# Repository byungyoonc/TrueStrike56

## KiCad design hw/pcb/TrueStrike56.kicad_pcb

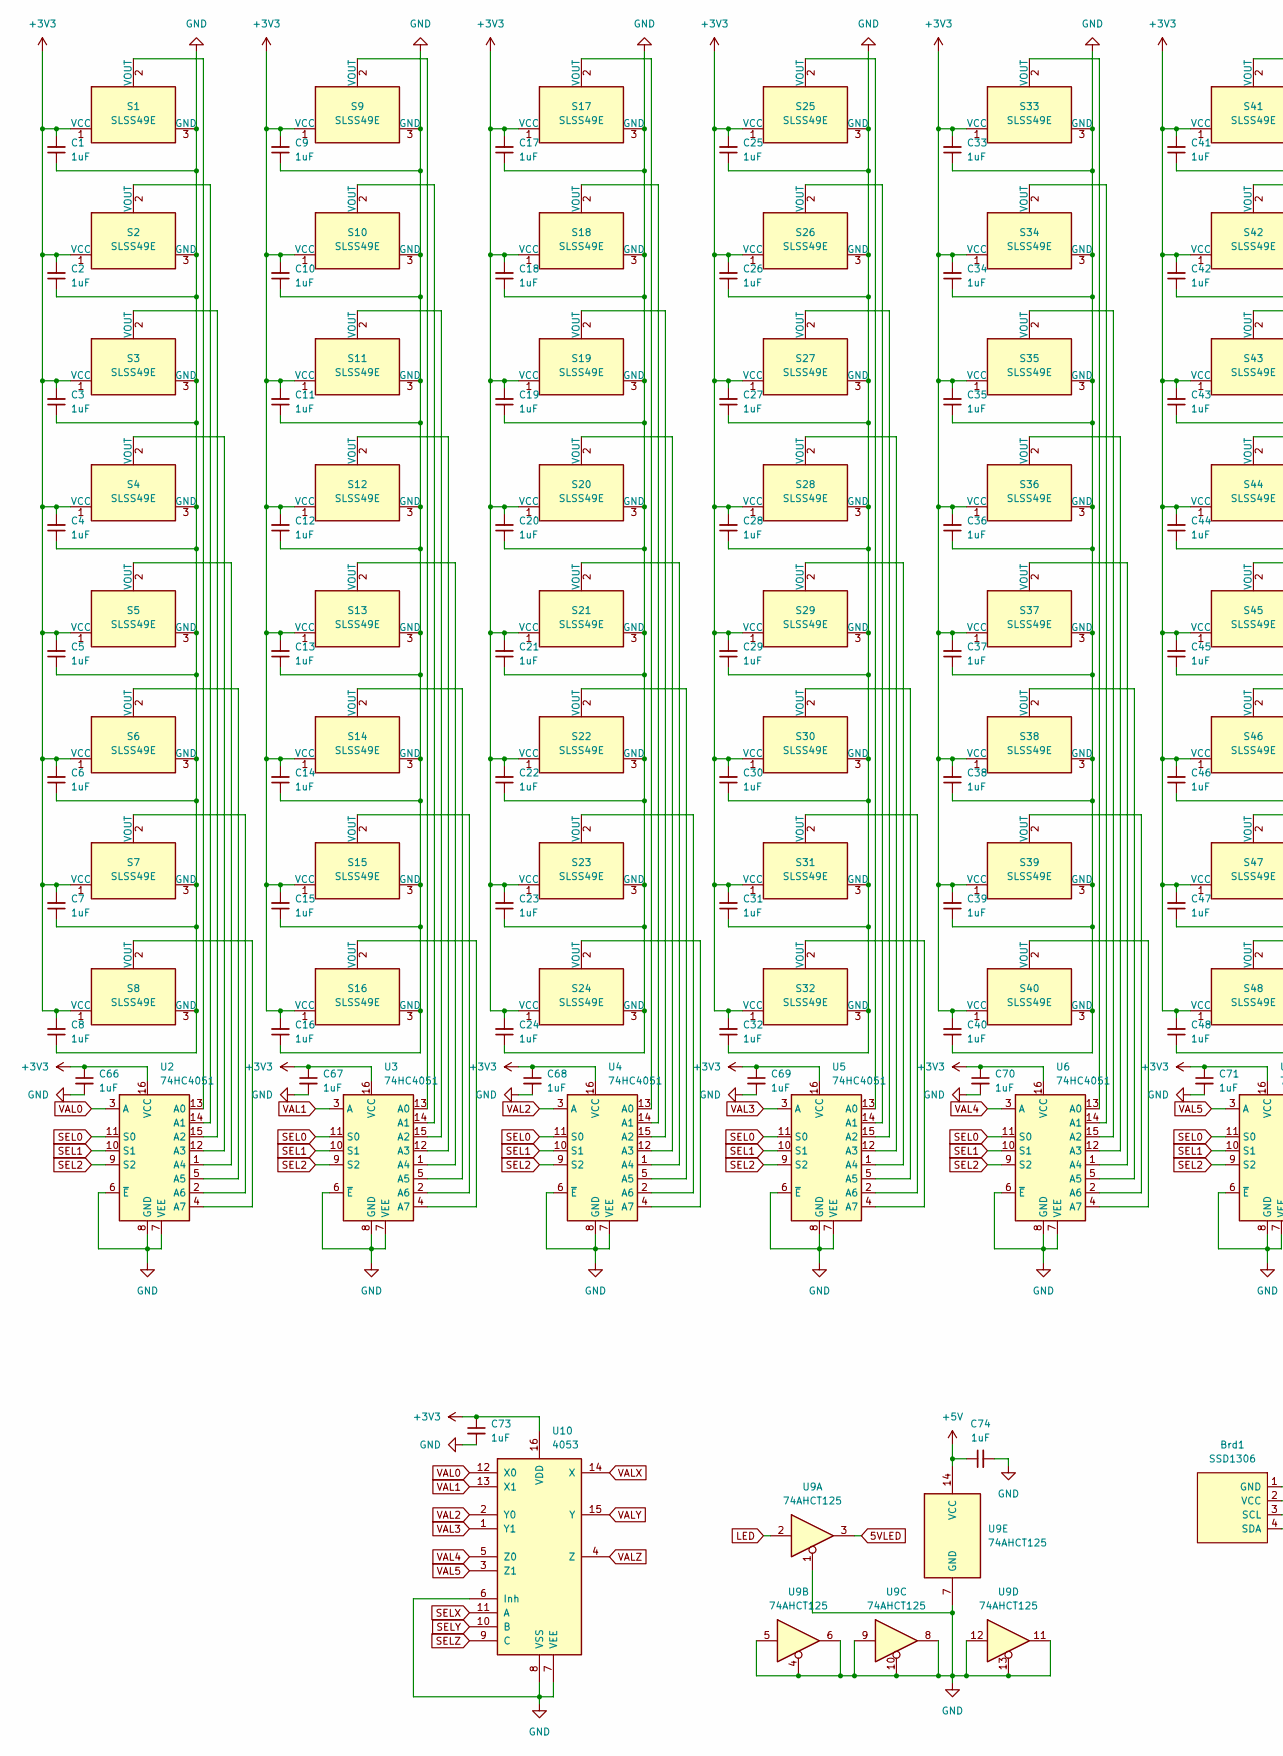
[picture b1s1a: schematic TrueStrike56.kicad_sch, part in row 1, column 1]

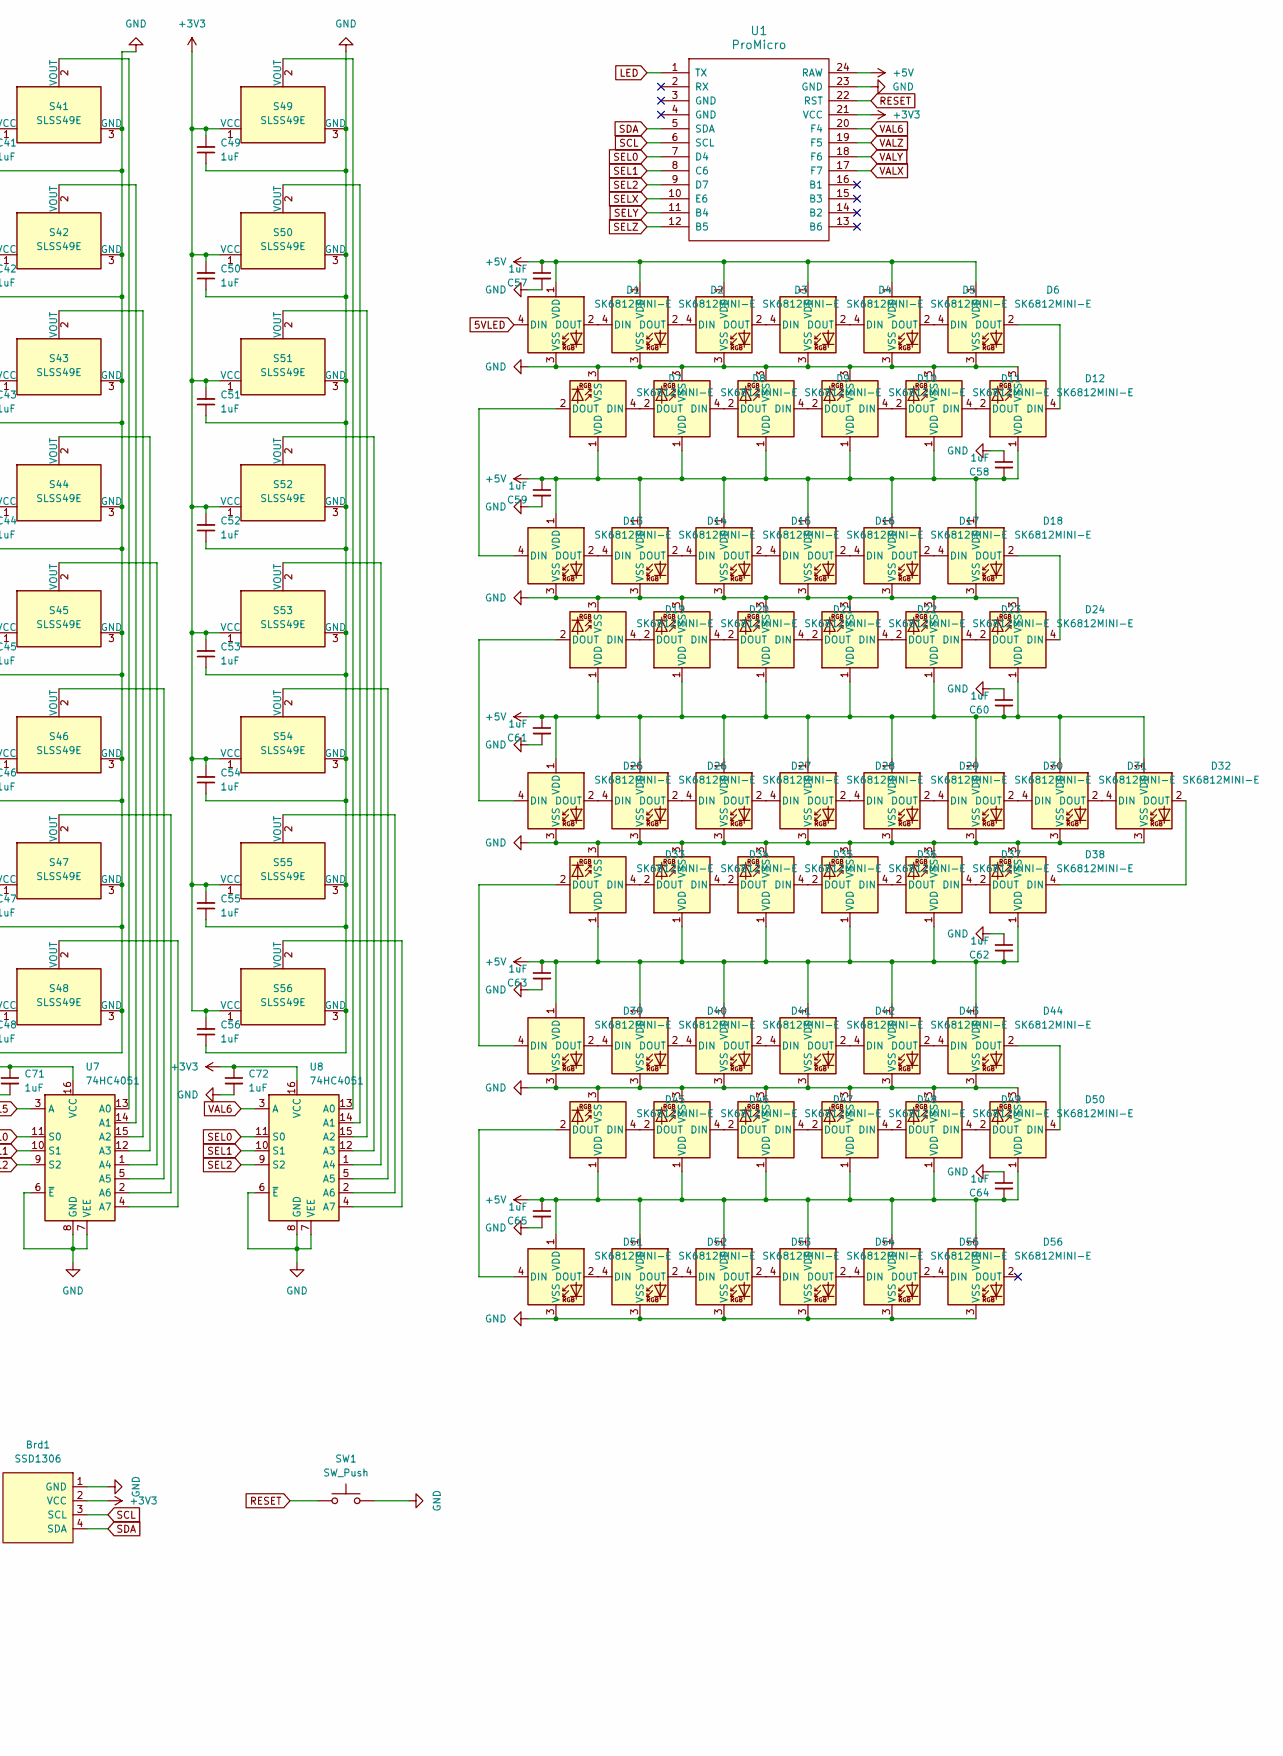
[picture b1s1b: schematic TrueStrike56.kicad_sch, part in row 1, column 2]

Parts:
Brd1: SSD1306; 128x64OLED
C1, C2, C3, C4, C5, C6, C7, C8, C9, C10, C11, C12, C13, C14, C15, C16, C17, C18, C19, C20, C21, C22, C23, C24, C25, C26, C27, C28, C29, C30, C31, C32, C33, C34, C35, C36, C37, C38, C39, C40, C41, C42, C43, C44, C45, C46, C47, C48, C49, C50, C51, C52, C53, C54, C55, C56, C57, C58, C59, C60, C61, C62, C63, C64, C65, C66, C67, C68, C69, C70, C71, C72, C73, C74: 1uF; C_0805_2012Metric_Pad1.18x1.45mm_HandSolder; LCSC Part # C28233
D1, D2, D3, D4, D5, D6, D13, D14, D15, D16, D17, D18, D33, D34, D35, D36, D37, D38, D45, D46, D47, D48, D49, D50: SK6812MINI-E; SK6812MINI-E_nusumi; LCSC Part # C5149201
D7, D8, D9, D10, D11, D12, D19, D20, D21, D22, D23, D24, D25, D26, D27, D28, D29, D30, D31, D32, D39, D40, D41, D42, D43, D44, D51, D52, D53, D54, D55, D56: SK6812MINI-E; SK6812MINI-E_nusumi_Rotated; LCSC Part # C5149201
S1, S2, S3, S4, S5, S6, S7, S8, S9, S10, S11, S12, S13, S14, S15, S16, S17, S18, S19, S20, S21, S22, S23, S24, S25, S26, S27, S28, S29, S30, S31, S32, S33, S34, S35, S36, S37, S38, S39, S40, S41, S42, S43, S44, S45, S46, S47, S48, S49, S50, S51, S54, S55, S56: SLSS49E; HE-Switch-1U; LCSC Part # C126669
S52, S53: SLSS49E; HE-Switch-1.5U; LCSC Part # C126669
SW1: SW_Push; SW_Push_1P1T_XKB_TS-1187A; LCSC Part # C318884
U1: ProMicro
U2, U3, U4, U5, U6, U7, U8: 74HC4051; SOIC-16_3.9x9.9mm_P1.27mm; LCSC Part # C85220
U9: 74AHCT125; SOIC-14_3.9x8.7mm_P1.27mm; LCSC Part # C155176
U10: 4053; SOIC-16_3.9x9.9mm_P1.27mm; LCSC Part # C5647

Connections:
5VLED: D1.4 (DIN), U9.3
+3V3: Brd1.2 (VCC), C1.2, C2.2, C3.2, C4.2, C5.2, C6.2, C7.2, C8.2, C9.2, C10.2, C11.2, C12.2, C13.2, C14.2, C15.2, C16.2, C17.2, C18.2, C19.2, C20.2, C21.2, C22.2, C23.2, C24.2, C25.2, C26.2, C27.2, C28.2, C29.2, C30.2, C31.2, C32.2, C33.2, C34.2, C35.2, C36.2, C37.2, C38.2, C39.2, C40.2, C41.2, C42.2, C43.2, C44.2, C45.2, C46.2, C47.2, C48.2, C49.2, C50.2, C51.2, C52.2, C53.2, C54.2, C55.2, C56.2, C66.1, C67.1, C68.1, C69.1, C70.1, C71.1, C72.1, C73.1, S1.1 (VCC), S2.1 (VCC), S3.1 (VCC), S4.1 (VCC), S5.1 (VCC), S6.1 (VCC), S7.1 (VCC), S8.1 (VCC), S9.1 (VCC), S10.1 (VCC), S11.1 (VCC), S12.1 (VCC), S13.1 (VCC), S14.1 (VCC), S15.1 (VCC), S16.1 (VCC), S17.1 (VCC), S18.1 (VCC), S19.1 (VCC), S20.1 (VCC), S21.1 (VCC), S22.1 (VCC), S23.1 (VCC), S24.1 (VCC), S25.1 (VCC), S26.1 (VCC), S27.1 (VCC), S28.1 (VCC), S29.1 (VCC), S30.1 (VCC), S31.1 (VCC), S32.1 (VCC), S33.1 (VCC), S34.1 (VCC), S35.1 (VCC), S36.1 (VCC), S37.1 (VCC), S38.1 (VCC), S39.1 (VCC), S40.1 (VCC), S41.1 (VCC), S42.1 (VCC), S43.1 (VCC), S44.1 (VCC), S45.1 (VCC), S46.1 (VCC), S47.1 (VCC), S48.1 (VCC), S49.1 (VCC), S50.1 (VCC), S51.1 (VCC), S52.1 (VCC), S53.1 (VCC), S54.1 (VCC), S55.1 (VCC), S56.1 (VCC), U1.21 (VCC), U2.16 (VCC), U3.16 (VCC), U4.16 (VCC), U5.16 (VCC), U6.16 (VCC), U7.16 (VCC), U8.16 (VCC), U10.16 (VDD)
+5V: C57.1, C58.2, C59.1, C60.2, C61.1, C62.2, C63.1, C64.2, C65.1, C74.1, D1.1 (VDD), D2.1 (VDD), D3.1 (VDD), D4.1 (VDD), D5.1 (VDD), D6.1 (VDD), D7.1 (VDD), D8.1 (VDD), D9.1 (VDD), D10.1 (VDD), D11.1 (VDD), D12.1 (VDD), D13.1 (VDD), D14.1 (VDD), D15.1 (VDD), D16.1 (VDD), D17.1 (VDD), D18.1 (VDD), D19.1 (VDD), D20.1 (VDD), D21.1 (VDD), D22.1 (VDD), D23.1 (VDD), D24.1 (VDD), D25.1 (VDD), D26.1 (VDD), D27.1 (VDD), D28.1 (VDD), D29.1 (VDD), D30.1 (VDD), D31.1 (VDD), D32.1 (VDD), D33.1 (VDD), D34.1 (VDD), D35.1 (VDD), D36.1 (VDD), D37.1 (VDD), D38.1 (VDD), D39.1 (VDD), D40.1 (VDD), D41.1 (VDD), D42.1 (VDD), D43.1 (VDD), D44.1 (VDD), D45.1 (VDD), D46.1 (VDD), D47.1 (VDD), D48.1 (VDD), D49.1 (VDD), D50.1 (VDD), D51.1 (VDD), D52.1 (VDD), D53.1 (VDD), D54.1 (VDD), D55.1 (VDD), D56.1 (VDD), U1.24 (RAW), U9.14 (VCC)
GND: Brd1.1 (GND), C1.1, C2.1, C3.1, C4.1, C5.1, C6.1, C7.1, C8.1, C9.1, C10.1, C11.1, C12.1, C13.1, C14.1, C15.1, C16.1, C17.1, C18.1, C19.1, C20.1, C21.1, C22.1, C23.1, C24.1, C25.1, C26.1, C27.1, C28.1, C29.1, C30.1, C31.1, C32.1, C33.1, C34.1, C35.1, C36.1, C37.1, C38.1, C39.1, C40.1, C41.1, C42.1, C43.1, C44.1, C45.1, C46.1, C47.1, C48.1, C49.1, C50.1, C51.1, C52.1, C53.1, C54.1, C55.1, C56.1, C57.2, C58.1, C59.2, C60.1, C61.2, C62.1, C63.2, C64.1, C65.2, C66.2, C67.2, C68.2, C69.2, C70.2, C71.2, C72.2, C73.2, C74.2, D1.3 (VSS), D2.3 (VSS), D3.3 (VSS), D4.3 (VSS), D5.3 (VSS), D6.3 (VSS), D7.3 (VSS), D8.3 (VSS), D9.3 (VSS), D10.3 (VSS), D11.3 (VSS), D12.3 (VSS), D13.3 (VSS), D14.3 (VSS), D15.3 (VSS), D16.3 (VSS), D17.3 (VSS), D18.3 (VSS), D19.3 (VSS), D20.3 (VSS), D21.3 (VSS), D22.3 (VSS), D23.3 (VSS), D24.3 (VSS), D25.3 (VSS), D26.3 (VSS), D27.3 (VSS), D28.3 (VSS), D29.3 (VSS), D30.3 (VSS), D31.3 (VSS), D32.3 (VSS), D33.3 (VSS), D34.3 (VSS), D35.3 (VSS), D36.3 (VSS), D37.3 (VSS), D38.3 (VSS), D39.3 (VSS), D40.3 (VSS), D41.3 (VSS), D42.3 (VSS), D43.3 (VSS), D44.3 (VSS), D45.3 (VSS), D46.3 (VSS), D47.3 (VSS), D48.3 (VSS), D49.3 (VSS), D50.3 (VSS), D51.3 (VSS), D52.3 (VSS), D53.3 (VSS), D54.3 (VSS), D55.3 (VSS), D56.3 (VSS), S1.3 (GND), S2.3 (GND), S3.3 (GND), S4.3 (GND), S5.3 (GND), S6.3 (GND), S7.3 (GND), S8.3 (GND), S9.3 (GND), S10.3 (GND), S11.3 (GND), S12.3 (GND), S13.3 (GND), S14.3 (GND), S15.3 (GND), S16.3 (GND), S17.3 (GND), S18.3 (GND), S19.3 (GND), S20.3 (GND), S21.3 (GND), S22.3 (GND), S23.3 (GND), S24.3 (GND), S25.3 (GND), S26.3 (GND), S27.3 (GND), S28.3 (GND), S29.3 (GND), S30.3 (GND), S31.3 (GND), S32.3 (GND), S33.3 (GND), S34.3 (GND), S35.3 (GND), S36.3 (GND), S37.3 (GND), S38.3 (GND), S39.3 (GND), S40.3 (GND), S41.3 (GND), S42.3 (GND), S43.3 (GND), S44.3 (GND), S45.3 (GND), S46.3 (GND), S47.3 (GND), S48.3 (GND), S49.3 (GND), S50.3 (GND), S51.3 (GND), S52.3 (GND), S53.3 (GND), S54.3 (GND), S55.3 (GND), S56.3 (GND), SW1.2, U1.23 (GND), U2.6 (~E), U2.7 (VEE), U2.8 (GND), U3.6 (~E), U3.7 (VEE), U3.8 (GND), U4.6 (~E), U4.7 (VEE), U4.8 (GND), U5.6 (~E), U5.7 (VEE), U5.8 (GND), U6.6 (~E), U6.7 (VEE), U6.8 (GND), U7.6 (~E), U7.7 (VEE), U7.8 (GND), U8.6 (~E), U8.7 (VEE), U8.8 (GND), U9.1, U9.4, U9.5, U9.6, U9.7 (GND), U9.8, U9.9, U9.10, U9.11, U9.12, U9.13, U10.6 (Inh), U10.7 (VEE), U10.8 (VSS)
LED: U1.1 (TX), U9.2
unnamed: D1.2 (DOUT), D2.4 (DIN)
unnamed: D2.2 (DOUT), D3.4 (DIN)
unnamed: D3.2 (DOUT), D4.4 (DIN)
unnamed: D4.2 (DOUT), D5.4 (DIN)
unnamed: D5.2 (DOUT), D6.4 (DIN)
unnamed: D7.4 (DIN), D8.2 (DOUT)
unnamed: D8.4 (DIN), D9.2 (DOUT)
unnamed: D10.4 (DIN), D11.2 (DOUT)
unnamed: D9.4 (DIN), D10.2 (DOUT)
unnamed: D11.4 (DIN), D12.2 (DOUT)
unnamed: D6.2 (DOUT), D12.4 (DIN)
unnamed: D7.2 (DOUT), D13.4 (DIN)
unnamed: D13.2 (DOUT), D14.4 (DIN)
unnamed: D14.2 (DOUT), D15.4 (DIN)
unnamed: D15.2 (DOUT), D16.4 (DIN)
unnamed: D16.2 (DOUT), D17.4 (DIN)
unnamed: D17.2 (DOUT), D18.4 (DIN)
unnamed: D18.2 (DOUT), D24.4 (DIN)
unnamed: D19.4 (DIN), D20.2 (DOUT)
unnamed: D19.2 (DOUT), D25.4 (DIN)
unnamed: D20.4 (DIN), D21.2 (DOUT)
unnamed: D21.4 (DIN), D22.2 (DOUT)
unnamed: D22.4 (DIN), D23.2 (DOUT)
unnamed: D23.4 (DIN), D24.2 (DOUT)
unnamed: D25.2 (DOUT), D26.4 (DIN)
unnamed: D26.2 (DOUT), D27.4 (DIN)
unnamed: D27.2 (DOUT), D28.4 (DIN)
unnamed: D28.2 (DOUT), D29.4 (DIN)
unnamed: D29.2 (DOUT), D30.4 (DIN)
unnamed: D30.2 (DOUT), D31.4 (DIN)
unnamed: D31.2 (DOUT), D32.4 (DIN)
unnamed: D32.2 (DOUT), D38.4 (DIN)
unnamed: D33.4 (DIN), D34.2 (DOUT)
unnamed: D33.2 (DOUT), D39.4 (DIN)
unnamed: D34.4 (DIN), D35.2 (DOUT)
unnamed: D35.4 (DIN), D36.2 (DOUT)
unnamed: D36.4 (DIN), D37.2 (DOUT)
unnamed: D37.4 (DIN), D38.2 (DOUT)
unnamed: D39.2 (DOUT), D40.4 (DIN)
unnamed: D40.2 (DOUT), D41.4 (DIN)
unnamed: D41.2 (DOUT), D42.4 (DIN)
unnamed: D42.2 (DOUT), D43.4 (DIN)
unnamed: D43.2 (DOUT), D44.4 (DIN)
unnamed: D44.2 (DOUT), D50.4 (DIN)
unnamed: D45.4 (DIN), D46.2 (DOUT)
unnamed: D45.2 (DOUT), D51.4 (DIN)
unnamed: D46.4 (DIN), D47.2 (DOUT)
unnamed: D47.4 (DIN), D48.2 (DOUT)
unnamed: D48.4 (DIN), D49.2 (DOUT)
unnamed: D49.4 (DIN), D50.2 (DOUT)
unnamed: D51.2 (DOUT), D52.4 (DIN)
unnamed: D52.2 (DOUT), D53.4 (DIN)
unnamed: D53.2 (DOUT), D54.4 (DIN)
unnamed: D54.2 (DOUT), D55.4 (DIN)
unnamed: D55.2 (DOUT), D56.4 (DIN)
unnamed: S1.2 (VOUT), U2.13 (A0)
unnamed: S2.2 (VOUT), U2.14 (A1)
unnamed: S3.2 (VOUT), U2.15 (A2)
unnamed: S4.2 (VOUT), U2.12 (A3)
unnamed: S5.2 (VOUT), U2.1 (A4)
unnamed: S6.2 (VOUT), U2.5 (A5)
unnamed: S7.2 (VOUT), U2.2 (A6)
unnamed: S8.2 (VOUT), U2.4 (A7)
unnamed: S9.2 (VOUT), U3.13 (A0)
unnamed: S10.2 (VOUT), U3.14 (A1)
unnamed: S11.2 (VOUT), U3.15 (A2)
unnamed: S12.2 (VOUT), U3.12 (A3)
unnamed: S13.2 (VOUT), U3.1 (A4)
unnamed: S14.2 (VOUT), U3.5 (A5)
unnamed: S15.2 (VOUT), U3.2 (A6)
unnamed: S16.2 (VOUT), U3.4 (A7)
unnamed: S17.2 (VOUT), U4.13 (A0)
unnamed: S18.2 (VOUT), U4.14 (A1)
unnamed: S19.2 (VOUT), U4.15 (A2)
unnamed: S20.2 (VOUT), U4.12 (A3)
unnamed: S21.2 (VOUT), U4.1 (A4)
unnamed: S22.2 (VOUT), U4.5 (A5)
unnamed: S23.2 (VOUT), U4.2 (A6)
unnamed: S24.2 (VOUT), U4.4 (A7)
unnamed: S25.2 (VOUT), U5.13 (A0)
unnamed: S26.2 (VOUT), U5.14 (A1)
unnamed: S27.2 (VOUT), U5.15 (A2)
unnamed: S28.2 (VOUT), U5.12 (A3)
unnamed: S29.2 (VOUT), U5.1 (A4)
unnamed: S30.2 (VOUT), U5.5 (A5)
unnamed: S31.2 (VOUT), U5.2 (A6)
unnamed: S32.2 (VOUT), U5.4 (A7)
unnamed: S33.2 (VOUT), U6.13 (A0)
unnamed: S34.2 (VOUT), U6.14 (A1)
unnamed: S35.2 (VOUT), U6.15 (A2)
unnamed: S36.2 (VOUT), U6.12 (A3)
unnamed: S37.2 (VOUT), U6.1 (A4)
unnamed: S38.2 (VOUT), U6.5 (A5)
unnamed: S39.2 (VOUT), U6.2 (A6)
unnamed: S40.2 (VOUT), U6.4 (A7)
unnamed: S41.2 (VOUT), U7.13 (A0)
unnamed: S42.2 (VOUT), U7.14 (A1)
unnamed: S43.2 (VOUT), U7.15 (A2)
unnamed: S44.2 (VOUT), U7.12 (A3)
unnamed: S45.2 (VOUT), U7.1 (A4)
unnamed: S46.2 (VOUT), U7.5 (A5)
unnamed: S47.2 (VOUT), U7.2 (A6)
unnamed: S48.2 (VOUT), U7.4 (A7)
unnamed: S49.2 (VOUT), U8.13 (A0)
unnamed: S50.2 (VOUT), U8.14 (A1)
unnamed: S51.2 (VOUT), U8.15 (A2)
unnamed: S52.2 (VOUT), U8.12 (A3)
unnamed: S53.2 (VOUT), U8.1 (A4)
unnamed: S54.2 (VOUT), U8.5 (A5)
unnamed: S55.2 (VOUT), U8.2 (A6)
unnamed: S56.2 (VOUT), U8.4 (A7)
RESET: SW1.1, U1.22 (RST)
SCL: Brd1.3 (SCL), U1.6 (SCL)
SDA: Brd1.4 (SDA), U1.5 (SDA)
SEL0: U1.7 (D4), U2.11 (S0), U3.11 (S0), U4.11 (S0), U5.11 (S0), U6.11 (S0), U7.11 (S0), U8.11 (S0)
SEL1: U1.8 (C6), U2.10 (S1), U3.10 (S1), U4.10 (S1), U5.10 (S1), U6.10 (S1), U7.10 (S1), U8.10 (S1)
SEL2: U1.9 (D7), U2.9 (S2), U3.9 (S2), U4.9 (S2), U5.9 (S2), U6.9 (S2), U7.9 (S2), U8.9 (S2)
SELX: U1.10 (E6), U10.11 (A)
SELY: U1.11 (B4), U10.10 (B)
SELZ: U1.12 (B5), U10.9 (C)
VAL0: U2.3 (A), U10.12 (X0)
VAL1: U3.3 (A), U10.13 (X1)
VAL2: U4.3 (A), U10.2 (Y0)
VAL3: U5.3 (A), U10.1 (Y1)
VAL4: U6.3 (A), U10.5 (Z0)
VAL5: U7.3 (A), U10.3 (Z1)
VAL6: U1.20 (F4), U8.3 (A)
VALX: U1.17 (F7), U10.14 (X)
VALY: U1.18 (F6), U10.15 (Y)
VALZ: U1.19 (F5), U10.4 (Z)

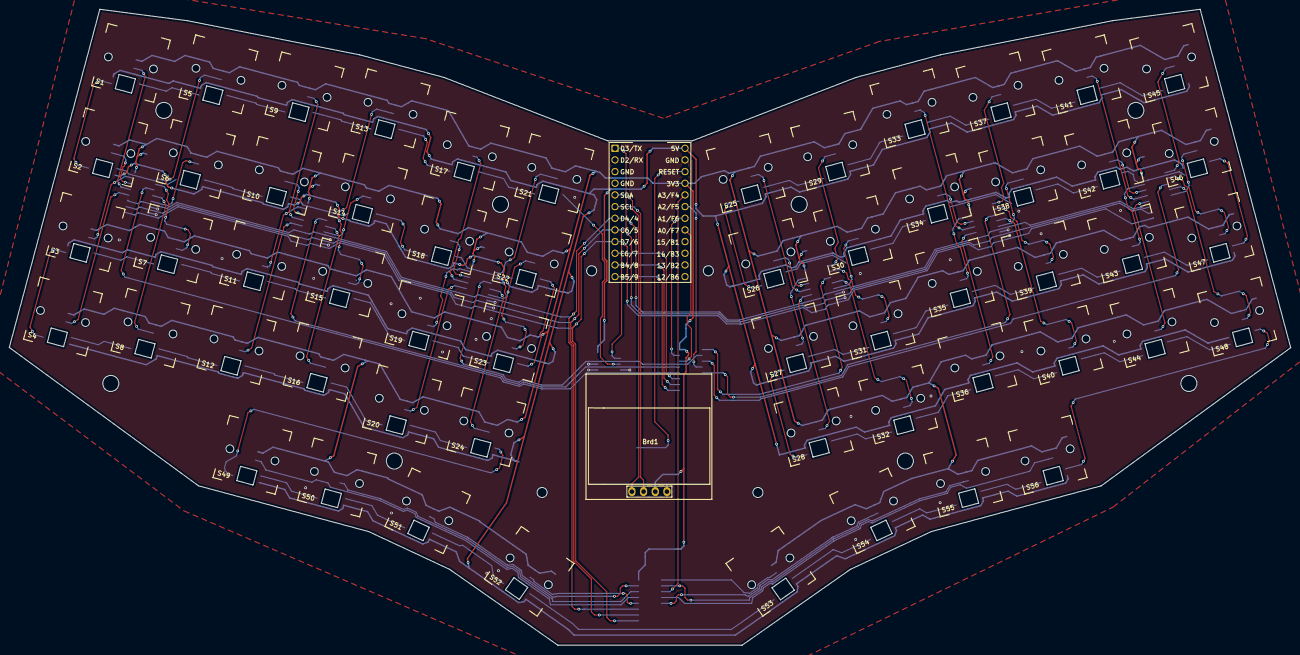
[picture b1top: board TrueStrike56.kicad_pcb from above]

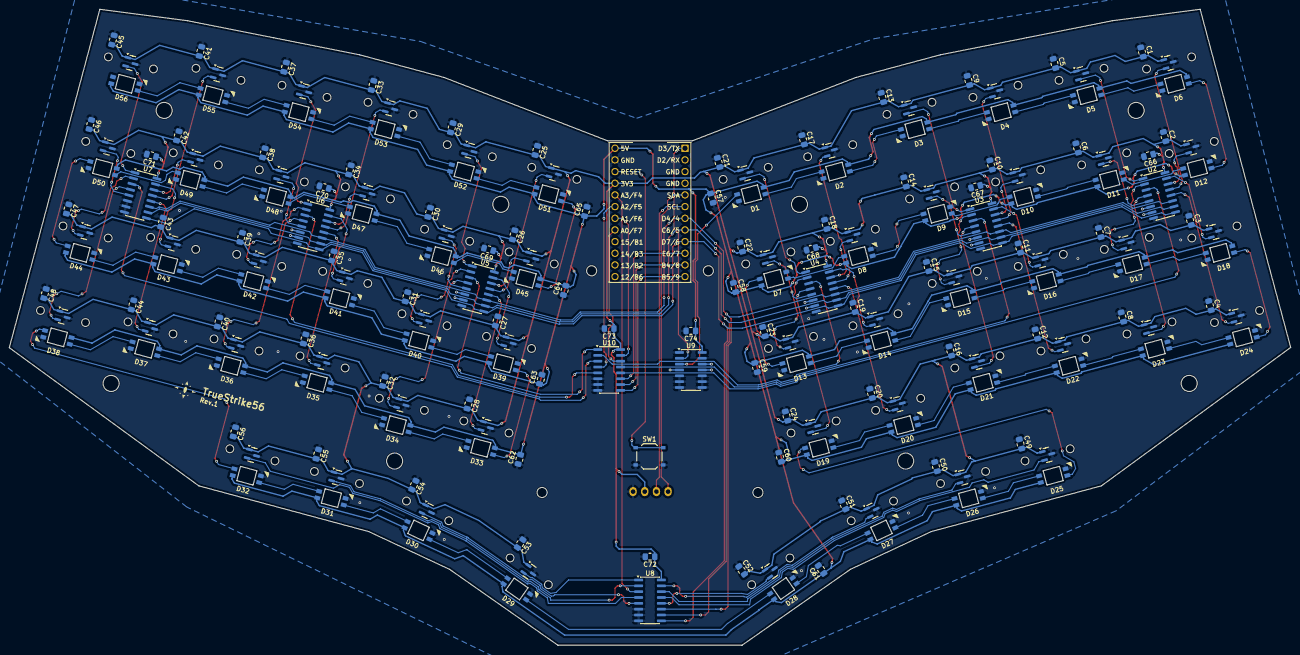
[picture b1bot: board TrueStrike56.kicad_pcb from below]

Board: 2 copper layers, 278.9 x 138.4 mm, 198 parts (196 on the bottom side), 135 nets.

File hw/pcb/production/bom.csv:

Designator,Footprint,Quantity,Value,LCSC Part #
"C1, C10, C11, C12, C13, C14, C15, C16, C17, C18, C19, C2, C20, C21, C22, C23, C24, C25, C26, C27, C28, C29, C3, C30, C31, C32, C33, C34, C35, C36, C37, C38, C39, C4, C40, C41, C42, C43, C44, C45, C46, C47, C48, C49, C5, C50, C51, C52, C53, C54, C55, C56, C57, C58, C59, C6, C60, C61, C62, C63, C64, C65, C66, C67, C68, C69, C7, C70, C71, C72, C73, C74, C8, C9",0805,74,1uF,C28233
"D1, D13, D14, D15, D16, D17, D18, D2, D3, D33, D34, D35, D36, D37, D38, D4, D45, D46, D47, D48, D49, D5, D50, D6",SK6812MINI-E_nusumi,24,SK6812MINI-E,C5149201
"D10, D11, D12, D19, D20, D21, D22, D23, D24, D25, D26, D27, D28, D29, D30, D31, D32, D39, D40, D41, D42, D43, D44, D51, D52, D53, D54, D55, D56, D7, D8, D9",SK6812MINI-E_nusumi_Rotated,32,SK6812MINI-E,C5149201
"S1, S10, S11, S12, S13, S14, S15, S16, S17, S18, S19, S2, S20, S21, S22, S23, S24, S25, S26, S27, S28, S29, S3, S30, S31, S32, S33, S34, S35, S36, S37, S38, S39, S4, S40, S41, S42, S43, S44, S45, S46, S47, S48, S49, S5, S50, S51, S54, S55, S56, S6, S7, S8, S9",HE-Switch-1U,54,SLSS49E,C126669
"S52, S53",HE-Switch-1.5U,2,SLSS49E,C126669
SW1,SW_Push_1P1T_XKB_TS-1187A,1,SW_Push,C318884
U10,SOIC-16_3.9x9.9mm_P1.27mm,1,4053,C5647
"U2, U3, U4, U5, U6, U7, U8",SOIC-16_3.9x9.9mm_P1.27mm,7,74HC4051,C85220
U9,SOIC-14_3.9x8.7mm_P1.27mm,1,74AHCT125,C155176

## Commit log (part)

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2026-02-09 Upload PCB design files + submodules
2026-02-09 feat(logo): init truestrike logo
2026-02-11 Add mounting holes and plates, MCU cover
2026-02-21 Add logo+model name+rev #, set LCSC Part # for PCBA order
2026-02-21 Add fabrication toolkit options set
2026-02-21 Add Gerber, production files
2026-02-21 Update PCB and production files for PCBA
    Changed RESET tactile switch to JLCPCB PCBA compatible part
2026-02-21 Add production files for the rest
2026-02-21 Update HE switch footprint to have the correct side
2026-05-12 Upload firmware files and codes
2026-05-12 Update VIA json file to have better layout & remove custom keycodes
2026-06-20 Add submodule for rollyboi
2026-06-20 Ignore production file backups
2026-06-20 Add bottom and top plates for rev2 HW
2026-06-20 Update existing kicad project version
2026-06-20 Add gerber output files for rev2 HW
2026-06-20 Add PCBA output files for rev2 PCB
2026-06-20 Update BOM's LCSC # based on JLCPCB inventory
2026-06-20 Update display text for rev1 FW
